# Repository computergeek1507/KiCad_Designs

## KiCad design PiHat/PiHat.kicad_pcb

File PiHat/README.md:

# Copyright and Disclaimer
Copyright: Scott Hanson

This documentation describes Open Hardware and is licensed under the CERN OHL v. 1.2.

You may redistribute and modify this documentation under the terms of the CERN OHL v.1.2. (http://ohwr.org/cernohl). This documentation is distributed WITHOUT ANY EXPRESS OR IMPLIED WARRANTY, INCLUDING OF MERCHANTABILITY, SATISFACTORY QUALITY AND FITNESS FOR A PARTICULAR PURPOSE. Please see the CERN OHL v.1.2 for applicable conditions

# Open Source PiHat

Open Source Pixel PiHat. A Raspberry Pi running FPP can drives 2 pixel ports and 1 serial port. The design was made with all through hole components for easy assembly by most users. Open source applications were used to create this controller. [KiCad](http://kicad-pcb.org/) was used for the PCB design, and [LibreOffice](https://www.libreoffice.org/) for the documentation.

To order your own PCB upload the gerber.zip file to your favorite PCB manufacture of choice, I personally use [jlcpcb.com](https://jlcpcb.com/).

Assembly Instructions are included in the manual below.

### Features
* Powered by FPP Falcon Player
* Standalone/Master/Remote/Bridge Support
* 2 3-Wire Pixel Ports
* 700 pixel per output at 40 FPS or 1300 at 20 FPS
* 1 DMX Serial Outputs
* Fused Powered DMX Output
* OLED Display header
* Adafruit Real Time Clock Header Connector
* 2 pin GPIO Header for Push Button or Relay Support
* 5v - 24v Vin Support

## [Part BOM](https://github.com/computergeek1507/KiCad_Designs/raw/master/PiHat/PiHat_BOM.ods)

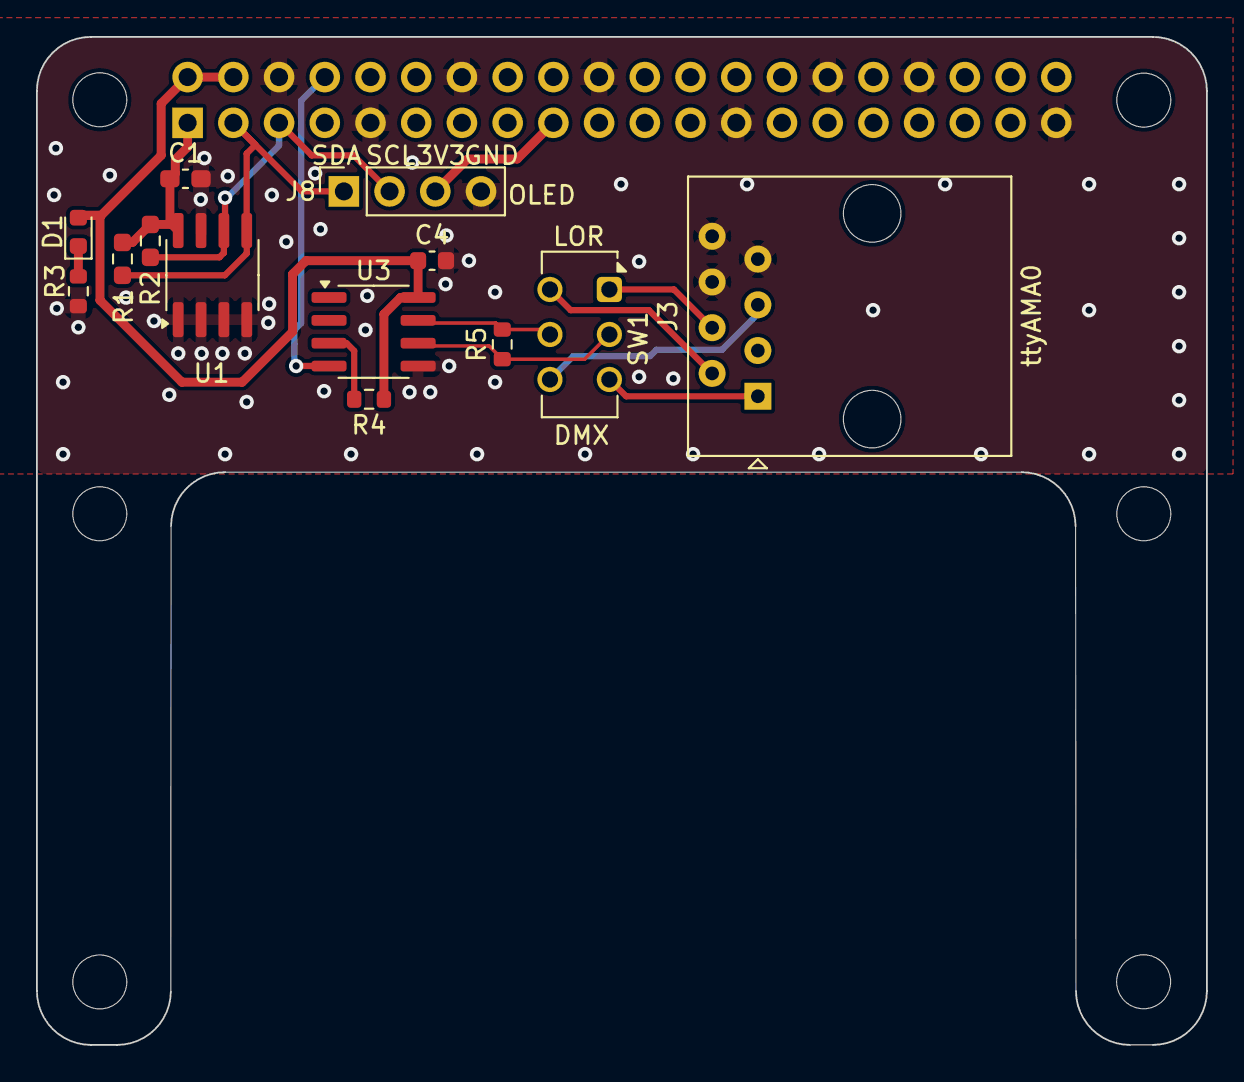
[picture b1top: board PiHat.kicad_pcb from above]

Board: 2 copper layers, 65.0 x 56.0 mm, 20 parts (1 on the bottom side), 14 nets.

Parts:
C1: 0.1uF; C_0603_1608Metric_Pad1.08x0.95mm_HandSolder
C4: 0.1uF; C_0603_1608Metric
D1: LED; LED_0603_1608Metric
H1, H2, H3, H4, H5, H6: 3mm_Mounting_Hole; MountingHole_3mm
J1: Raspberry_Pi_2_3; PinSocket_2x20_P2.54mm_Vertical
J3: DMX1 RJ45; RJ45_Amphenol_54602-x08_Horizontal
J8: OLED; PinSocket_1x04_P2.54mm_Vertical
R1, R2: 4.7K; R_0603_1608Metric_Pad0.98x0.95mm_HandSolder
R3, R5: 120; R_0603_1608Metric
R4: 10K; R_0603_1608Metric
SW1: DMX_LOR_Select; SW_CK_JS202011CQN_DPDT_Straight
U1: 24LC256; SOIC-8_3.9x4.9mm_P1.27mm
U3: SP3485CP; SOIC-8_3.9x4.9mm_P1.27mm

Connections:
+3.3V: C1.1, J1.1 (3V3), J1.17 (3V3), J8.3, R1.2, R2.2, U1.8 (VCC)
+5V: C4.1, D1.2 (A), J1.2 (5V), J1.4 (5V), R4.1, U3.8 (VCC)
/DMX+: R5.1, SW1.2 (B), U3.6 (A)
/DMX-: R5.2, SW1.5 (B), U3.7 (B)
GND: C1.2, C4.2, J1.6 (GND), J1.9 (GND), J1.14 (GND), J1.20 (GND), J1.25 (GND), J1.30 (GND), J1.34 (GND), J1.39 (GND), J3.6, J3.7, J3.8, J8.4, R3.2, U1.1 (A0), U1.2 (A1), U1.3 (A2), U1.4 (GND), U1.7 (WP), U3.5 (GND)
I2C_SCL: J1.5 (SCL/GPIO3), J8.2, R2.1, U1.6 (SCL)
I2C_SDA: J1.3 (SDA/GPIO2), J8.1, R1.1, U1.5 (SDA)
unnamed: D1.1 (K), R3.1
unnamed: J3.4, SW1.1 (A)
unnamed: J3.1, SW1.3 (C)
unnamed: J3.5, SW1.4 (A)
unnamed: J3.2, SW1.6 (C)
unnamed: R4.2, U3.3 (DE)
TXD: J1.8 (GPIO14/TXD), U3.4 (DI)

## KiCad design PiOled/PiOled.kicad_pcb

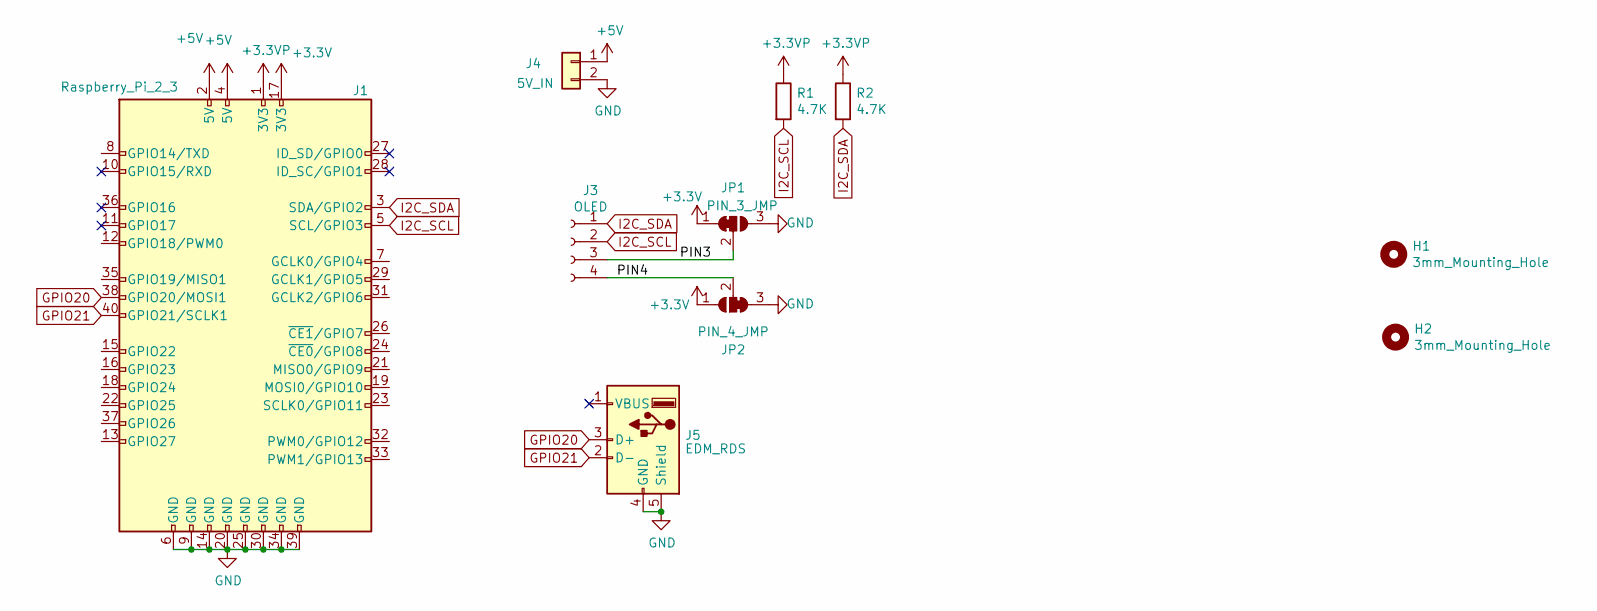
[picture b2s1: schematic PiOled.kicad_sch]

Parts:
H1, H2: 3mm_Mounting_Hole; MountingHole_3mm
J1: Raspberry_Pi_2_3; PinSocket_2x20_P2.54mm_Vertical; MPN PPPC202LFBN-RC; Digi-Key_PN S7123-ND
J3: OLED; PinSocket_1x04_P2.54mm_Vertical; MPN PPTC041LFBN-RC; Digi-Key_PN S7002-ND
J4: 5V_IN; TerminalBlock_Phoenix_MKDS-1,5-2_1x02_P5.00mm_Horizontal; MPN ED2675-ND; Digi-Key_PN OSTT7020150
J5: EDM_RDS; USB_A_Molex_67643_Horizontal
JP1: PIN_3_JMP; SolderJumper-3_P1mm_Bridged12
JP2: PIN_4_JMP; SolderJumper-3_P1mm_Bridged23
R1, R2: 4.7K; R_0805_2012Metric_Pad1.20x1.40mm_HandSolder

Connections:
+3.3VP: J1.1 (3V3), R1.1, R2.1
+3V3: J1.17 (3V3), JP1.1 (A), JP2.1 (A)
+5V: J1.2 (5V), J1.4 (5V), J4.1
/PIN3: J3.3, JP1.2 (C)
/PIN4: J3.4, JP2.2 (C)
GND: J1.6 (GND), J1.9 (GND), J1.14 (GND), J1.20 (GND), J1.25 (GND), J1.30 (GND), J1.34 (GND), J1.39 (GND), J4.2, J5.4 (GND), J5.5 (Shield), JP1.3 (B), JP2.3 (B)
GPIO20: J1.38 (GPIO20/MOSI1), J5.3 (D+)
GPIO21: J1.40 (GPIO21/SCLK1), J5.2 (D-)
I2C_SCL: J1.5 (SCL/GPIO3), J3.2, R1.2
I2C_SDA: J1.3 (SDA/GPIO2), J3.1, R2.2

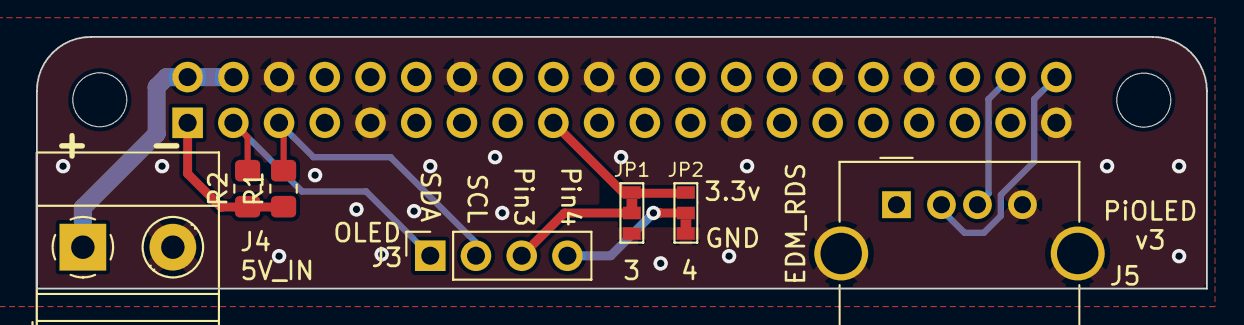
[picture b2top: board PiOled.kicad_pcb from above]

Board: 2 copper layers, 65.0 x 14.0 mm, 10 parts (1 on the bottom side), 10 nets.

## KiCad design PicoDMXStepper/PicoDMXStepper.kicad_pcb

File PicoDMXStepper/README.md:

# Copyright and Disclaimer
Copyright: Scott Hanson

This documentation describes Open Hardware and is licensed under the CERN OHL v. 1.2.

You may redistribute and modify this documentation under the terms of the CERN OHL v.1.2. (http://ohwr.org/cernohl). This documentation is distributed WITHOUT ANY EXPRESS OR IMPLIED WARRANTY, INCLUDING OF MERCHANTABILITY, SATISFACTORY QUALITY AND FITNESS FOR A PARTICULAR PURPOSE. Please see the CERN OHL v.1.2 for applicable conditions

# Pico DMX to Stepper

Drive Stepper Moter With DMX. SW2 configures steps per DMX Value. Open source applications were used to create this controller. [KiCad](http://kicad-pcb.org/) was used for the PCB design, and [LibreOffice](https://www.libreoffice.org/) for the documentation.

To order your own PCB upload the gerber.zip file to your favorite PCB manufacture of choice, I personally use [jlcpcb.com](https://jlcpcb.com/).

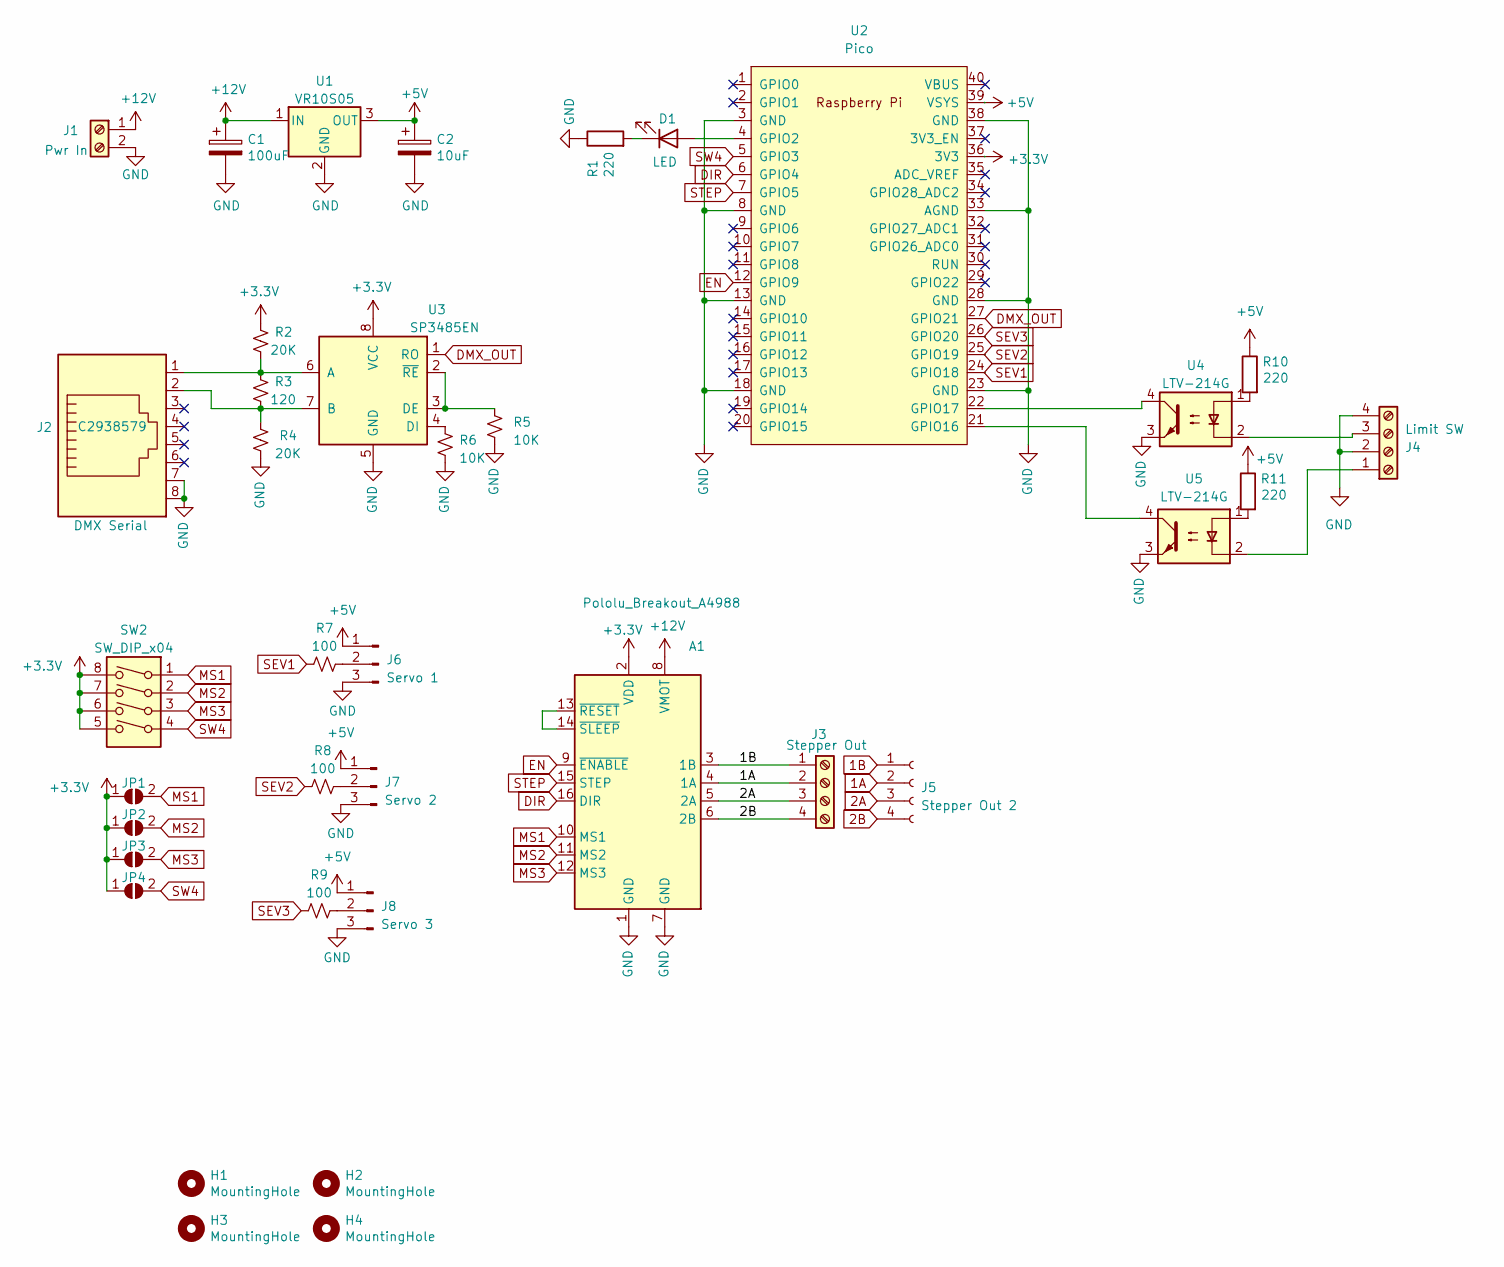
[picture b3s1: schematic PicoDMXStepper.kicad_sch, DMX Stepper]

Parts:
A1: Pololu_Breakout_A4988; Pololu_Breakout-16_15.2x20.3mm
C1: 100uF; C_Elec_8x10.2; LCSC C445063
C2: 10uF; C_0603_1608Metric_Pad1.08x0.95mm_HandSolder; LCSC C19702
D1: LED; LED_0603_1608Metric_Pad1.05x0.95mm_HandSolder; LCSC C72043
H1, H2, H3, H4: MountingHole; MountingHole_3.7mm
J1: Pwr In; BARRIER_BLOCK_1ROW_2POS_P8.26MM; LCSC C306200
J2: DMX Serial; RJ45_Amphenol_54602-x08_Horizontal; LCSC C2938579
J3: Stepper Out; TerminalBlock_Phoenix_MKDS-1,5-4_1x04_P5.00mm_Horizontal; LCSC C192779
J4: Limit SW; PhoenixContact_MCV_1,5_4-G-3.81_1x04_P3.81mm_Vertical; LCSC_PN C430599
J5: Stepper Out 2; JST_XH_B4B-XH-A_1x04_P2.50mm_Vertical
J6: Servo 1; PinHeader_1x03_P2.54mm_Vertical
J7: Servo 2; PinHeader_1x03_P2.54mm_Vertical
J8: Servo 3; PinHeader_1x03_P2.54mm_Vertical
JP1: MS1; SolderJumper-2_P1.3mm_Open_Pad1.0x1.5mm
JP2: MS2; SolderJumper-2_P1.3mm_Open_Pad1.0x1.5mm
JP3: MS3; SolderJumper-2_P1.3mm_Open_Pad1.0x1.5mm
JP4: SW4; SolderJumper-2_P1.3mm_Open_Pad1.0x1.5mm
R1, R10, R11: 220; R_0603_1608Metric_Pad0.98x0.95mm_HandSolder; LCSC C23345
R2, R4: 20K; R_0603_1608Metric_Pad0.98x0.95mm_HandSolder; LCSC_PN C4184
R3: 120; R_0603_1608Metric_Pad0.98x0.95mm_HandSolder; LCSC C72043
R5, R6: 10K; R_0603_1608Metric_Pad0.98x0.95mm_HandSolder; LCSC C25804
R7, R8, R9: 100; R_0603_1608Metric_Pad0.98x0.95mm_HandSolder
SW2: SW_DIP_x04; SW_DIP_SPSTx04_Slide_6.7x11.72mm_W7.62mm_P2.54mm_LowProfile; LCSC C509571
U1: VR10S05; MPN VR10S05; Digi-Key_PN 1470-VR10S05-ND
U2: Pico; RPi_Pico_SMD_TH
U3: SP3485EN; SOIC-8_3.9x4.9mm_P1.27mm; LCSC_PN C8963
U4, U5: LTV-214G; LTV214; LCSC C133122

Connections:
1A: A1.4 (1A), J3.2, J5.2
1B: A1.3 (1B), J3.1, J5.1
2A: A1.5 (2A), J3.3, J5.3
2B: A1.6 (2B), J3.4, J5.4
+3V3: A1.2 (VDD), JP1.1 (A), JP2.1 (A), JP3.1 (A), JP4.1 (A), R2.1, SW2.5, SW2.6, SW2.7, SW2.8, U2.36 (3V3), U3.8 (VCC)
+5V: C2.1, J6.1, J7.1, J8.1, R10.1, R11.1, U1.3 (OUT), U2.39 (VSYS)
+12V: A1.8 (VMOT), C1.1, J1.1, U1.1 (IN)
DIR: A1.16 (DIR), U2.6 (GPIO4)
DMX_OUT: U2.27 (GPIO21), U3.1 (RO)
EN: A1.9 (~ENABLE), U2.12 (GPIO9)
GND: A1.1 (GND), A1.7 (GND), C1.2, C2.2, J1.2, J2.7, J2.8, J4.2, J4.4, J6.3, J7.3, J8.3, R1.1, R4.2, R5.2, R6.2, U1.2 (GND), U2.3 (GND), U2.8 (GND), U2.13 (GND), U2.18 (GND), U2.23 (GND), U2.28 (GND), U2.33 (AGND), U2.38 (GND), U3.5 (GND), U4.3, U5.3
MS1: A1.10 (MS1), JP1.2 (B), SW2.1
MS2: A1.11 (MS2), JP2.2 (B), SW2.2
MS3: A1.12 (MS3), JP3.2 (B), SW2.3
unnamed: A1.13 (~RESET), A1.14 (~SLEEP)
unnamed: D1.2 (A), U2.4 (GPIO2)
unnamed: D1.1 (K), R1.2
unnamed: J4.1, U5.2
unnamed: J4.3, U4.2
unnamed: J6.2, R7.2
unnamed: J7.2, R8.2
unnamed: J8.2, R9.2
unnamed: R10.2, U4.1
unnamed: R11.2, U5.1
unnamed: U2.21 (GPIO16), U5.4
unnamed: U2.22 (GPIO17), U4.4
unnamed: J2.1, R2.2, R3.1, U3.6 (A)
unnamed: J2.2, R3.2, R4.1, U3.7 (B)
unnamed: R5.1, U3.2 (~RE), U3.3 (DE)
unnamed: R6.1, U3.4 (DI)
SEV1: R7.1, U2.24 (GPIO18)
SEV2: R8.1, U2.25 (GPIO19)
SEV3: R9.1, U2.26 (GPIO20)
STEP: A1.15 (STEP), U2.7 (GPIO5)
SW4: JP4.2 (B), SW2.4, U2.5 (GPIO3)

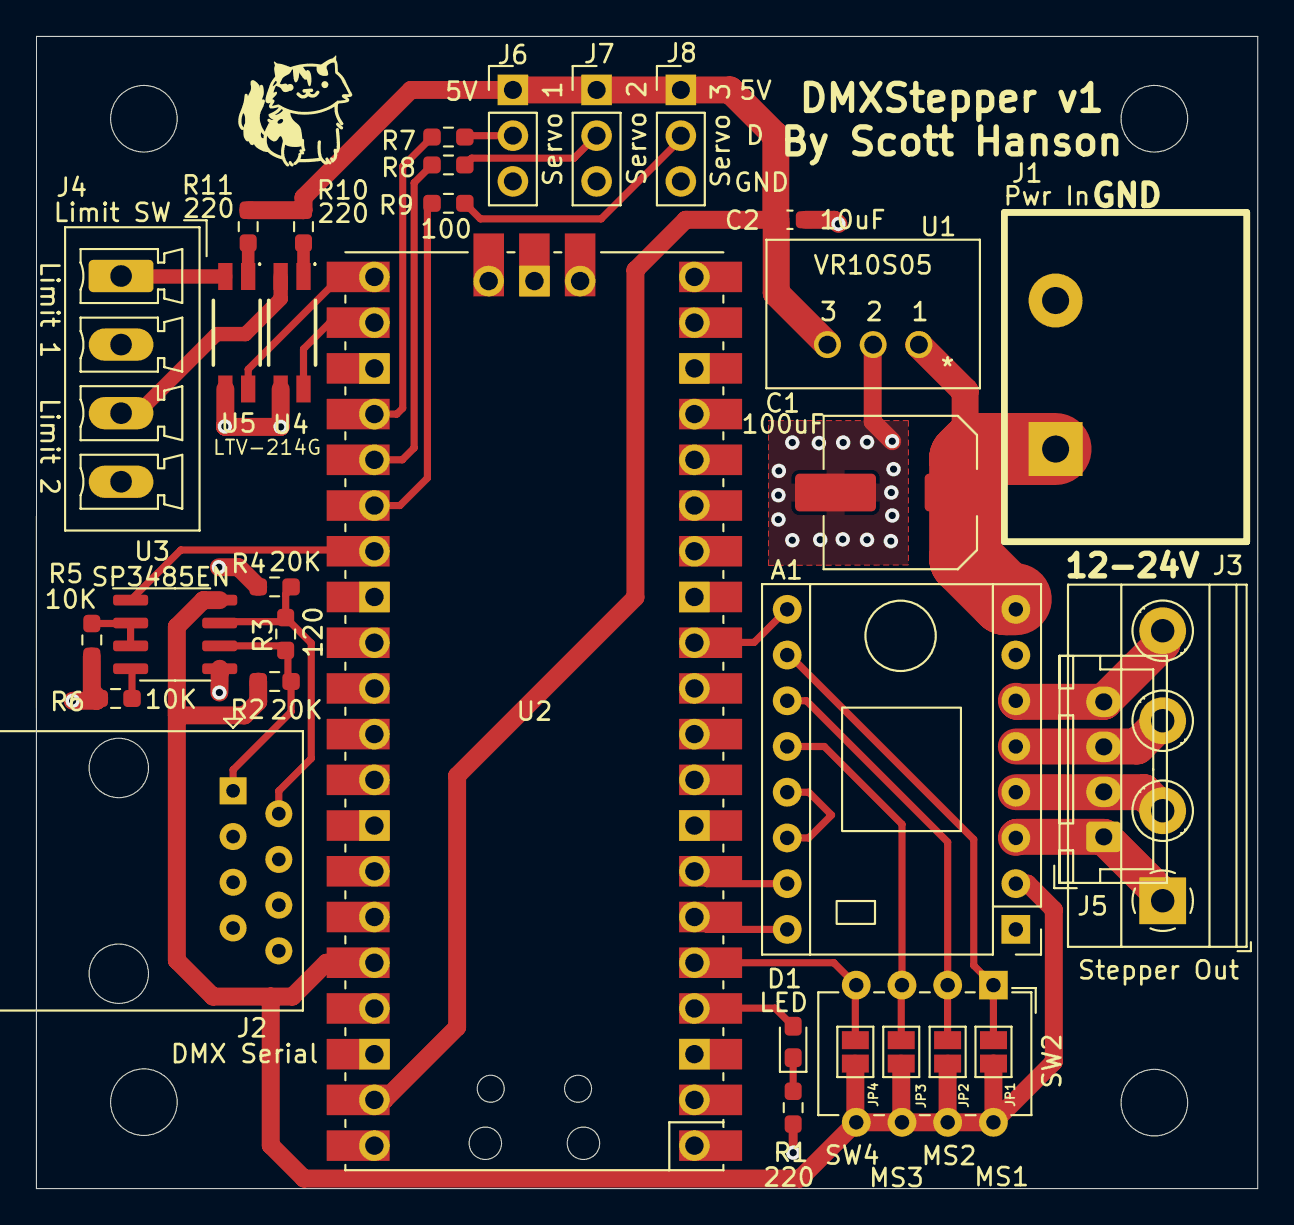
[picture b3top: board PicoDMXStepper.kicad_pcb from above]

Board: 2 copper layers, 67.8 x 64.0 mm, 37 parts (0 on the bottom side), 35 nets.

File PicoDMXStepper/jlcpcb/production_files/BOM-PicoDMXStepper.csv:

Comment,Designator,Footprint,LCSC
Servo 1,"J6,J7,J8",PinHeader_1x03_P2.54mm_Vertical,C124376
LTV-214G,"U4,U5",LTV214,C133122
Stepper Out 2,J5,JST_XH_B4B-XH-A_1x04_P2.50mm_Vertical,C144395
Stepper Out,J3,"TerminalBlock_Phoenix_MKDS-1,5-4_1x04_P5.00mm_Horizontal",C192779
10uF,C2,C_0603_1608Metric_Pad1.08x0.95mm_HandSolder,C19702
100,"R7,R8,R9",R_0603_1608Metric_Pad0.98x0.95mm_HandSolder,C22775
120,R3,R_0603_1608Metric_Pad0.98x0.95mm_HandSolder,C22787
220,"R1,R10,R11",R_0603_1608Metric_Pad0.98x0.95mm_HandSolder,C23345
10K,"R5,R6",R_0603_1608Metric_Pad0.98x0.95mm_HandSolder,C25804
DMX Serial,J2,RJ45_Amphenol_54602-x08_Horizontal,C2938579
Pwr In,J1,BARRIER_BLOCK_1ROW_2POS_P8.26MM,C306200
20K,"R2,R4",R_0603_1608Metric_Pad0.98x0.95mm_HandSolder,C4184
100uF,C1,C_Elec_8x10.2,C445063
SW_DIP_x04,SW2,SW_DIP_SPSTx04_Slide_6.7x11.72mm_W7.62mm_P2.54mm_LowProfile,C509571
Limit SW,J4,"PhoenixContact_MCV_1,5_4-G-3.81_1x04_P3.81mm_Vertical",C69809
LED,D1,LED_0603_1608Metric_Pad1.05x0.95mm_HandSolder,C72043
SP3485EN,U3,SOIC-8_3.9x4.9mm_P1.27mm,C8963
Pololu_Breakout_A4988,A1,Pololu_Breakout-16_15.2x20.3mm,
Pico,U2,RPi_Pico_SMD_TH,
VR10S05,U1,VR10S05,

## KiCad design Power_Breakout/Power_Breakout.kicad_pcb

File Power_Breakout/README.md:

# Copyright and Disclaimer
Copyright: Scott Hanson

This documentation describes Open Hardware and is licensed under the CERN OHL v. 1.2.

You may redistribute and modify this documentation under the terms of the CERN OHL v.1.2. (http://ohwr.org/cernohl). This documentation is distributed WITHOUT ANY EXPRESS OR IMPLIED WARRANTY, INCLUDING OF MERCHANTABILITY, SATISFACTORY QUALITY AND FITNESS FOR A PARTICULAR PURPOSE. Please see the CERN OHL v.1.2 for applicable conditions

# Power Breakout

Power Breakout Board for HP Power Supply

# BOM
| Component | Qty | Description              | Digi-Key PN     | Manufacturer          | Manufacturer PN |
|-----------|-----|--------------------------|-----------------|-----------------------|-----------------|
| J1,J2     |  2  | CONN 4 POS STRIP 0.374"  | ED2955-ND       | On Shore Technology   | OSTYK51104030   |
| J3        |  1  | CONN EDGE DUAL 64POS 0.1 | 1761469-1-ND    | TE Connectivity       | 1761469-1       |
| R1        |  1  | RES 120 OHM 1/4W 5%      | CF14JT120RCT-ND | Stackpole Electronics | CF14JT120R      |
| SW1       |  1  | SWITCH SLIDE SPDT        | 679-1849-ND     | APEM                  | MHSS1105        |

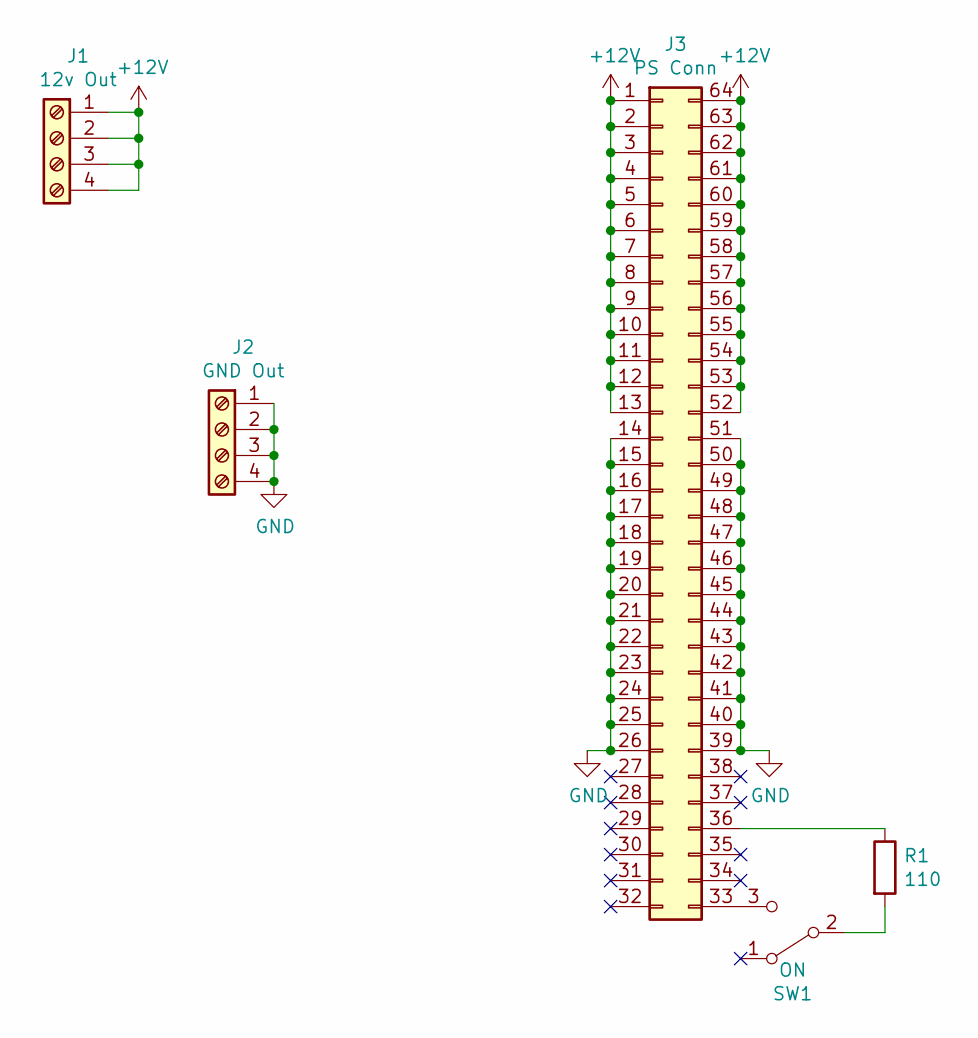
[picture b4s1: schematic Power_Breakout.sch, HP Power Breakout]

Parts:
J1: 12v Out; BARRIER_BLOCK_1ROW_4POS_P9.5MM
J2: GND Out; BARRIER_BLOCK_1ROW_4POS_P9.5MM
J3: PS Conn; TE_1761469-1
R1: 110; R_Axial_DIN0207_L6.3mm_D2.5mm_P7.62mm_Horizontal
SW1: ON; switch_mmp122-r

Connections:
+12V: J1.1, J1.2, J1.3, J1.4, J3.1, J3.2, J3.3, J3.4, J3.5, J3.6, J3.7, J3.8, J3.9, J3.10, J3.11, J3.12, J3.13, J3.52, J3.53, J3.54, J3.55, J3.56, J3.57, J3.58, J3.59, J3.60, J3.61, J3.62, J3.63, J3.64
GND: J2.1, J2.2, J2.3, J2.4, J3.14, J3.15, J3.16, J3.17, J3.18, J3.19, J3.20, J3.21, J3.22, J3.23, J3.24, J3.25, J3.26, J3.39, J3.40, J3.41, J3.42, J3.43, J3.44, J3.45, J3.46, J3.47, J3.48, J3.49, J3.50, J3.51
unnamed: J3.33, SW1.3 (C)
unnamed: J3.36, R1.1
unnamed: R1.2, SW1.2 (B)

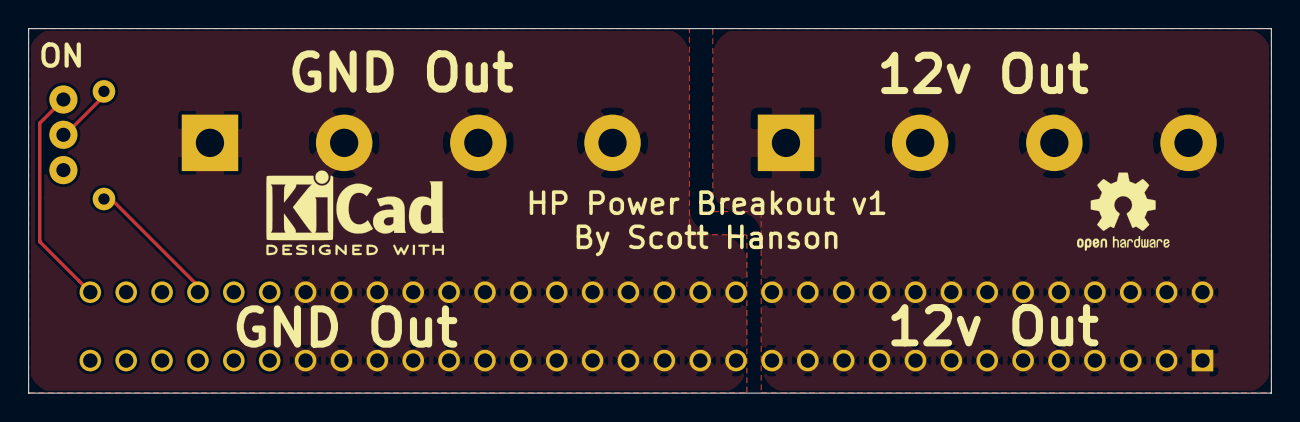
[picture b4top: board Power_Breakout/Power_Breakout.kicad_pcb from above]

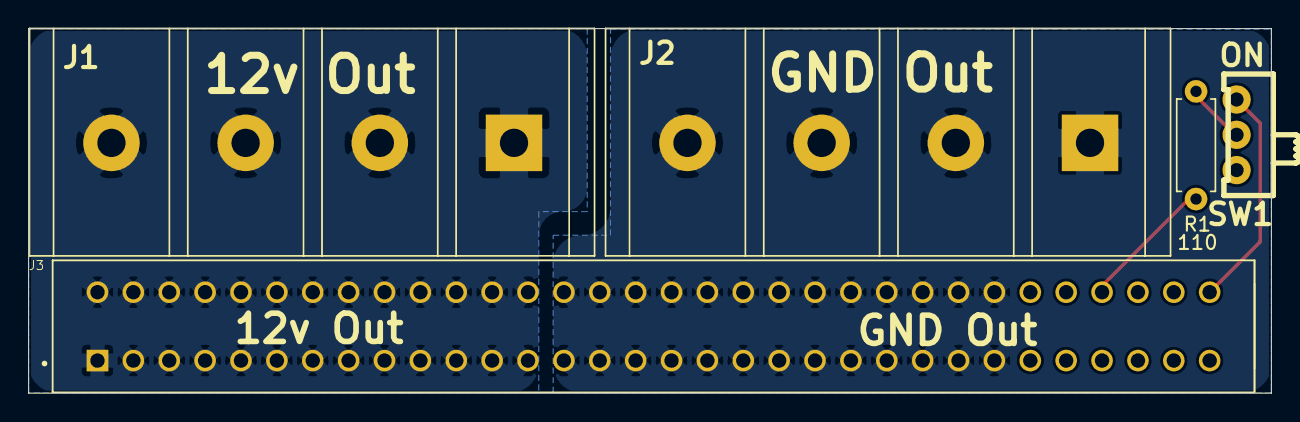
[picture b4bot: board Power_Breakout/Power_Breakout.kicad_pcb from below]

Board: 2 copper layers, 88.0 x 25.8 mm, 5 parts (5 on the bottom side), 5 nets.

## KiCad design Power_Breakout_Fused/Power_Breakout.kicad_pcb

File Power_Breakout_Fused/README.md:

# Copyright and Disclaimer
Copyright: Scott Hanson

This documentation describes Open Hardware and is licensed under the CERN OHL v. 1.2.

You may redistribute and modify this documentation under the terms of the CERN OHL v.1.2. (http://ohwr.org/cernohl). This documentation is distributed WITHOUT ANY EXPRESS OR IMPLIED WARRANTY, INCLUDING OF MERCHANTABILITY, SATISFACTORY QUALITY AND FITNESS FOR A PARTICULAR PURPOSE. Please see the CERN OHL v.1.2 for applicable conditions

# Power Breakout

Power Fused Breakout Board for HP Power Supply

# BOM
| Component   | Qty | Description              | Digi-Key PN     | Manufacturer          | Manufacturer PN |
|-------------|-----|--------------------------|-----------------|-----------------------|-----------------|
| D1          |  1  | LED GREEN 3MM            | 732-5008-ND     | Würth Elektronik      | 151031VS06000   |
| J1,J2       |  2  | CONN 4 POS STRIP 0.374"  | ED2955-ND       | On Shore Technology   | OSTYK51104030   |
| F1,F2,F3,F4 |  4  | FUSE HOLDER BLADE 30A    | 36-3568-ND      | Keystone Electronics  | 3568            |
| F1,F2,F3,F4 |  4  | FUSE AUTO 15A BLADE MINI | F992-ND         | Littelfuse            | 0297015.WXNV    |
| J3          |  1  | CONN EDGE DUAL 64POS 0.1 | 1761469-1-ND    | TE Connectivity       | 1761469-1       |
| R1          |  1  | RES 120 OHM 1/4W 5%      | CF14JT120RCT-ND | Stackpole Electronics | CF14JT120R      |
| R2          |  1  | RES 1K OHM 1/4W 5%       | CF14JT1K00CT-ND | Stackpole Electronics | CF14JT1K00      |
| SW1         |  1  | SWITCH SLIDE SPDT        | 679-1849-ND     | APEM                  | MHSS1105        |

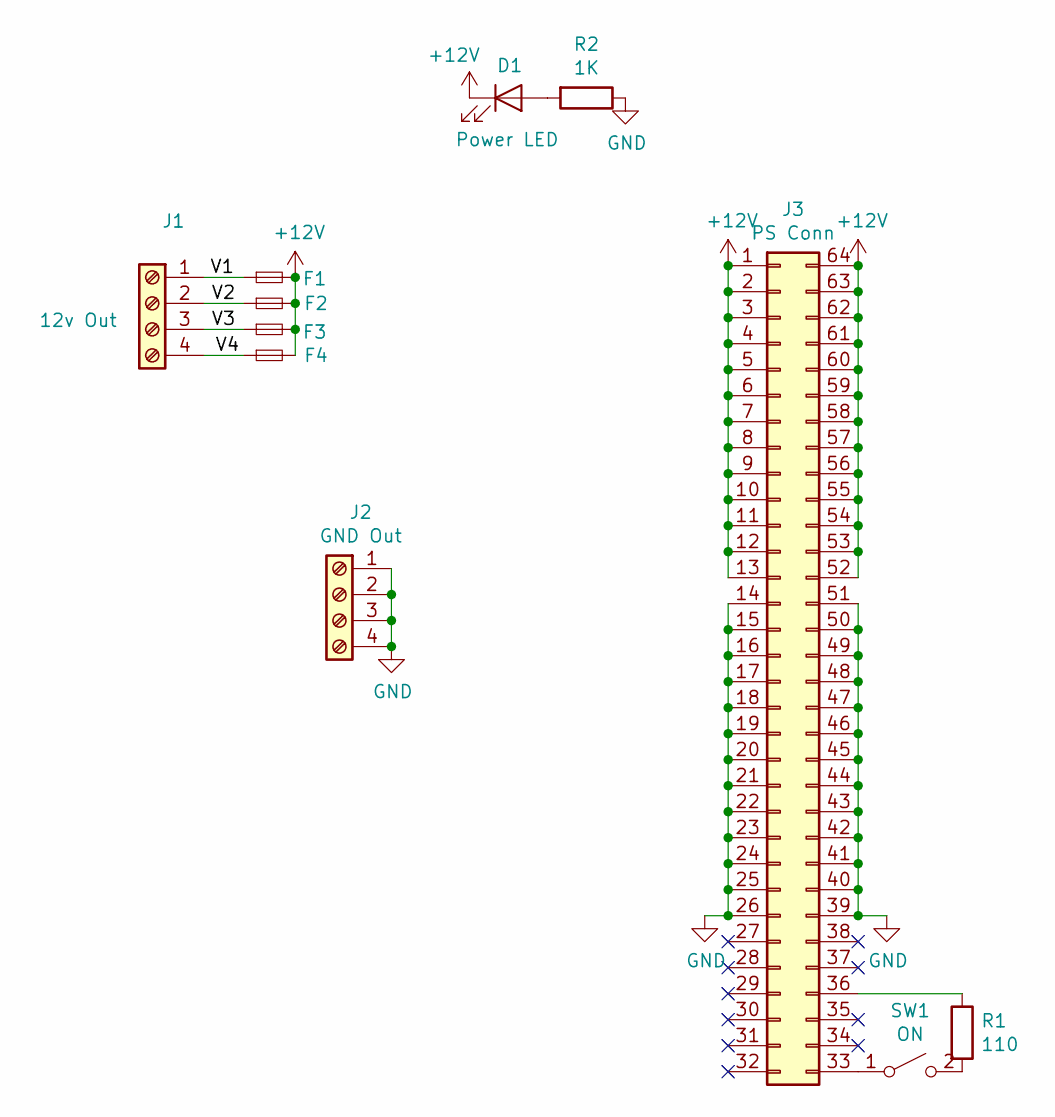
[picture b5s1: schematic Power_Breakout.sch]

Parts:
D1: Power LED; LED_D3.0mm_Clear
F1, F2, F3, F4: Fuse_Small; Fuseholder_Blade_Mini_Keystone_3568
J1: 12v Out; BARRIER_BLOCK_1ROW_4POS_P9.5MM
J2: GND Out; BARRIER_BLOCK_1ROW_4POS_P9.5MM
J3: PS Conn; TE_1761469-1
R1: 110; R_Axial_DIN0207_L6.3mm_D2.5mm_P7.62mm_Horizontal
R2: 1K; R_Axial_DIN0207_L6.3mm_D2.5mm_P7.62mm_Horizontal
SW1: ON; switch_mmp122-r

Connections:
+12V: D1.1 (K), F1.2, F2.2, F3.2, F4.2, J3.1, J3.2, J3.3, J3.4, J3.5, J3.6, J3.7, J3.8, J3.9, J3.10, J3.11, J3.12, J3.13, J3.52, J3.53, J3.54, J3.55, J3.56, J3.57, J3.58, J3.59, J3.60, J3.61, J3.62, J3.63, J3.64
/V1: F1.1, J1.1
/V2: F2.1, J1.2
/V3: F3.1, J1.3
/V4: F4.1, J1.4
GND: J2.1, J2.2, J2.3, J2.4, J3.14, J3.15, J3.16, J3.17, J3.18, J3.19, J3.20, J3.21, J3.22, J3.23, J3.24, J3.25, J3.26, J3.39, J3.40, J3.41, J3.42, J3.43, J3.44, J3.45, J3.46, J3.47, J3.48, J3.49, J3.50, J3.51, R2.1
unnamed: D1.2 (A), R2.2
unnamed: J3.33, SW1.1 (A)
unnamed: J3.36, R1.1
unnamed: R1.2, SW1.2 (B)

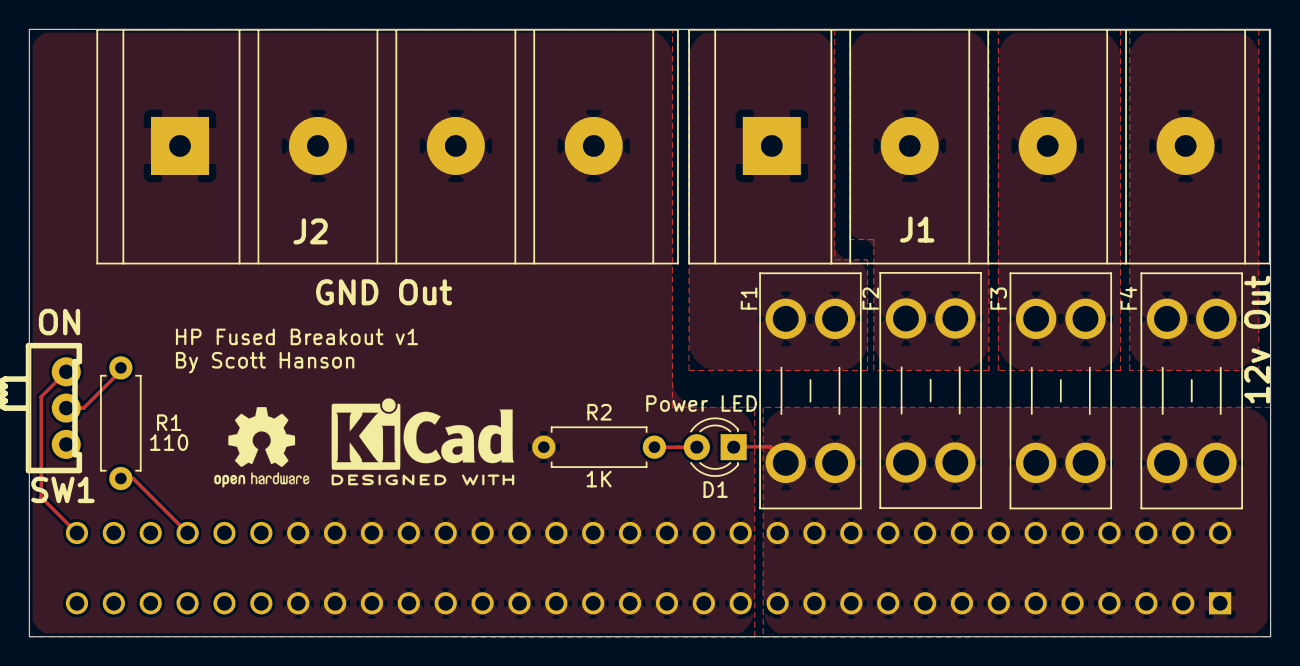
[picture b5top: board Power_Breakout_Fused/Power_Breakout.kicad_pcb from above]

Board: 2 copper layers, 85.5 x 41.8 mm, 11 parts (1 on the bottom side), 10 nets.

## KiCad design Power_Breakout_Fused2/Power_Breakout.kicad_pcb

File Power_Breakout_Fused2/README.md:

# Copyright and Disclaimer
Copyright: Scott Hanson

This documentation describes Open Hardware and is licensed under the CERN OHL v. 1.2.

You may redistribute and modify this documentation under the terms of the CERN OHL v.1.2. (http://ohwr.org/cernohl). This documentation is distributed WITHOUT ANY EXPRESS OR IMPLIED WARRANTY, INCLUDING OF MERCHANTABILITY, SATISFACTORY QUALITY AND FITNESS FOR A PARTICULAR PURPOSE. Please see the CERN OHL v.1.2 for applicable conditions

# Fused Power Breakout

Power Fused Breakout Board for HP Power Supply
<!--
# BOM
| Component   | Qty | Description              | Digi-Key PN     | Manufacturer          | Manufacturer PN |
|-------------|-----|--------------------------|-----------------|-----------------------|-----------------|
| D1          |  1  | LED GREEN 3MM            | 732-5008-ND     | Würth Elektronik      | 151031VS06000   |
| J1,J2       |  2  | CONN 4 POS STRIP 0.374"  | ED2955-ND       | On Shore Technology   | OSTYK51104030   |
| F1,F2,F3,F4 |  4  | FUSE HOLDER BLADE 30A    | 36-3568-ND      | Keystone Electronics  | 3568            |
| F1,F2,F3,F4 |  4  | FUSE AUTO 15A BLADE MINI | F992-ND         | Littelfuse            | 0297015.WXNV    |
| J3          |  1  | CONN EDGE DUAL 64POS 0.1 | 1761469-1-ND    | TE Connectivity       | 1761469-1       |
| R1          |  1  | RES 120 OHM 1/4W 5%      | CF14JT120RCT-ND | Stackpole Electronics | CF14JT120R      |
| R2          |  1  | RES 1K OHM 1/4W 5%       | CF14JT1K00CT-ND | Stackpole Electronics | CF14JT1K00      |
-->

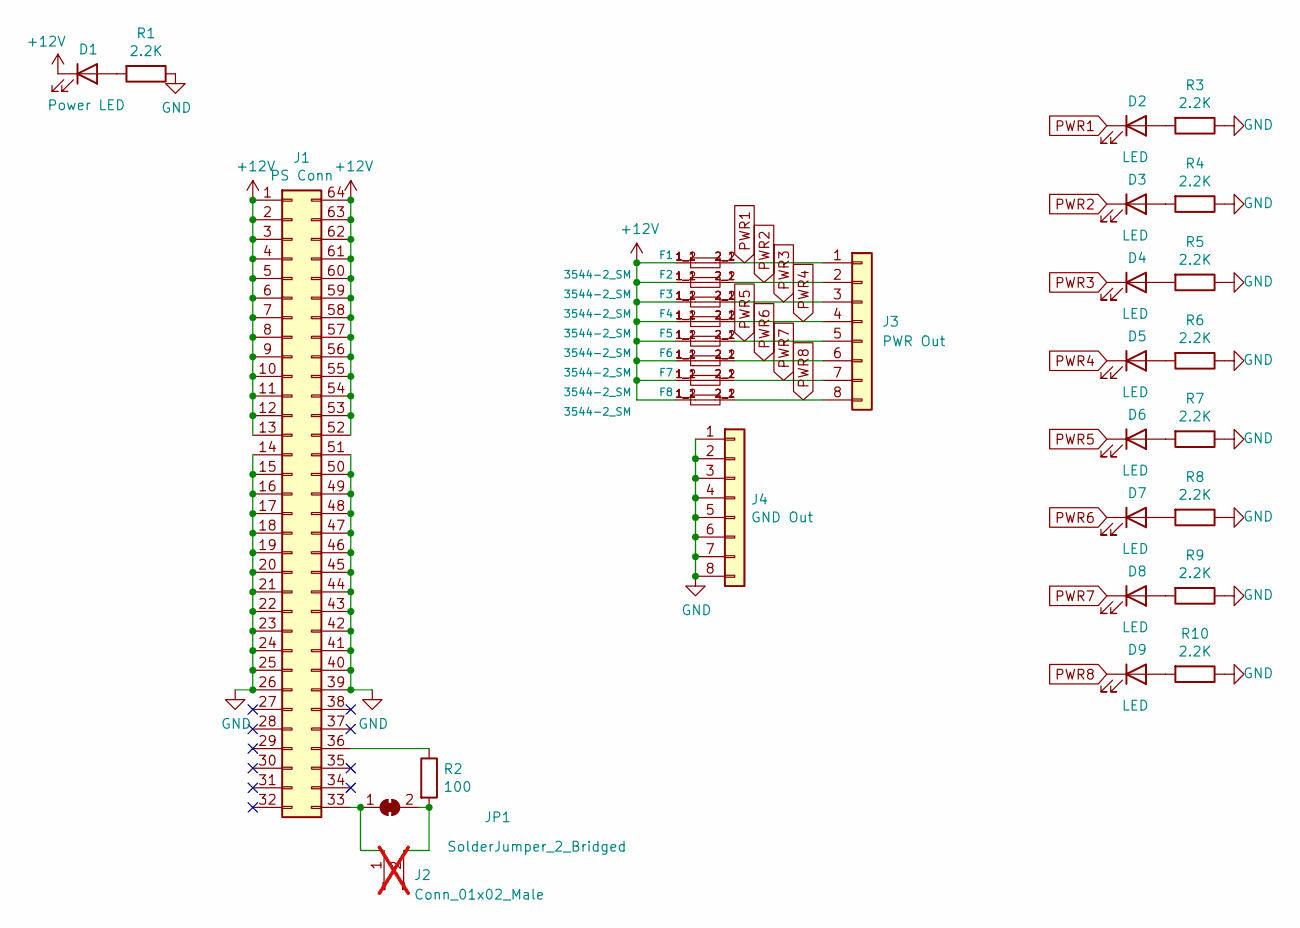
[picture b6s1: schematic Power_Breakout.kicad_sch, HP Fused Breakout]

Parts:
D1: Power LED; LED_0603_1608Metric; MPN LTST-C190KRKT; Digi-Key PN 160-1436-1-ND
D2, D3, D4, D5, D6, D7, D8, D9: LED; LED_0402_1005Metric; MPN QBLP595-IG; Digi-Key PN 1516-1216-1-ND
F1, F2, F3, F4, F5, F6, F7, F8: 3544-2_SM; FUSE_3544-2; MPN 3544-2; Digi-Key PN 36-3544-2-ND
J1: PS Conn; TE_1761469-1; MPN 1761468-1; Digi-Key PN A102052-ND
J2: Conn_01x02_Male; PinHeader_1x02_P2.54mm_Vertical; not fitted
J3: PWR Out; PhoenixContact_MCV_1,5_8-G-5.08_1x08_P5.08mm_Vertical; MPN VI0821550000G; Digi-Key PN 609-3942-ND
J4: GND Out; PhoenixContact_MCV_1,5_8-G-5.08_1x08_P5.08mm_Vertical; MPN VI0821550000G; Digi-Key PN 609-3942-ND
JP1: SolderJumper_2_Bridged; SolderJumper-2_P1.3mm_Bridged_Pad1.0x1.5mm
R1: 2.2K; R_0603_1608Metric; MPN RC0603FR-072K2L; Digi-Key PN 311-2.20KHRCT-ND
R2: 100; R_0603_1608Metric; MPN RC0603FR-07100RL; Digi-Key PN 311-100HRCT-ND
R3, R4, R5, R6, R7, R8, R9, R10: 2.2K; R_0402_1005Metric; MPN RC0402FR-072K2L; Digi-Key PN 311-2.20KLRCT-ND

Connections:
+12V: D1.1 (K), F1.1_1 (1), F1.1_2 (1), F2.1_1 (1), F2.1_2 (1), F3.1_1 (1), F3.1_2 (1), F4.1_1 (1), F4.1_2 (1), F5.1_1 (1), F5.1_2 (1), F6.1_1 (1), F6.1_2 (1), F7.1_1 (1), F7.1_2 (1), F8.1_1 (1), F8.1_2 (1), J1.1, J1.2, J1.3, J1.4, J1.5, J1.6, J1.7, J1.8, J1.9, J1.10, J1.11, J1.12, J1.13, J1.52, J1.53, J1.54, J1.55, J1.56, J1.57, J1.58, J1.59, J1.60, J1.61, J1.62, J1.63, J1.64
GND: J1.14, J1.15, J1.16, J1.17, J1.18, J1.19, J1.20, J1.21, J1.22, J1.23, J1.24, J1.25, J1.26, J1.39, J1.40, J1.41, J1.42, J1.43, J1.44, J1.45, J1.46, J1.47, J1.48, J1.49, J1.50, J1.51, J4.1, J4.2, J4.3, J4.4, J4.5, J4.6, J4.7, J4.8, R1.1, R3.1, R4.1, R5.1, R6.1, R7.1, R8.1, R9.1, R10.1
unnamed: D1.2 (A), R1.2
unnamed: D2.2 (A), R3.2
unnamed: D3.2 (A), R4.2
unnamed: D4.2 (A), R5.2
unnamed: D5.2 (A), R6.2
unnamed: D6.2 (A), R7.2
unnamed: D7.2 (A), R8.2
unnamed: D8.2 (A), R9.2
unnamed: D9.2 (A), R10.2
unnamed: J1.33, J2.1, JP1.1 (A)
unnamed: J1.36, R2.1
unnamed: J2.2, JP1.2 (B), R2.2
PWR1: D2.1 (K), F1.2_1 (2), F1.2_2 (2), J3.1
PWR2: D3.1 (K), F2.2_1 (2), F2.2_2 (2), J3.2
PWR3: D4.1 (K), F3.2_1 (2), F3.2_2 (2), J3.3
PWR4: D5.1 (K), F4.2_1 (2), F4.2_2 (2), J3.4
PWR5: D6.1 (K), F5.2_1 (2), F5.2_2 (2), J3.5
PWR6: D7.1 (K), F6.2_1 (2), F6.2_2 (2), J3.6
PWR7: D8.1 (K), F7.2_1 (2), F7.2_2 (2), J3.7
PWR8: D9.1 (K), F8.2_1 (2), F8.2_2 (2), J3.8

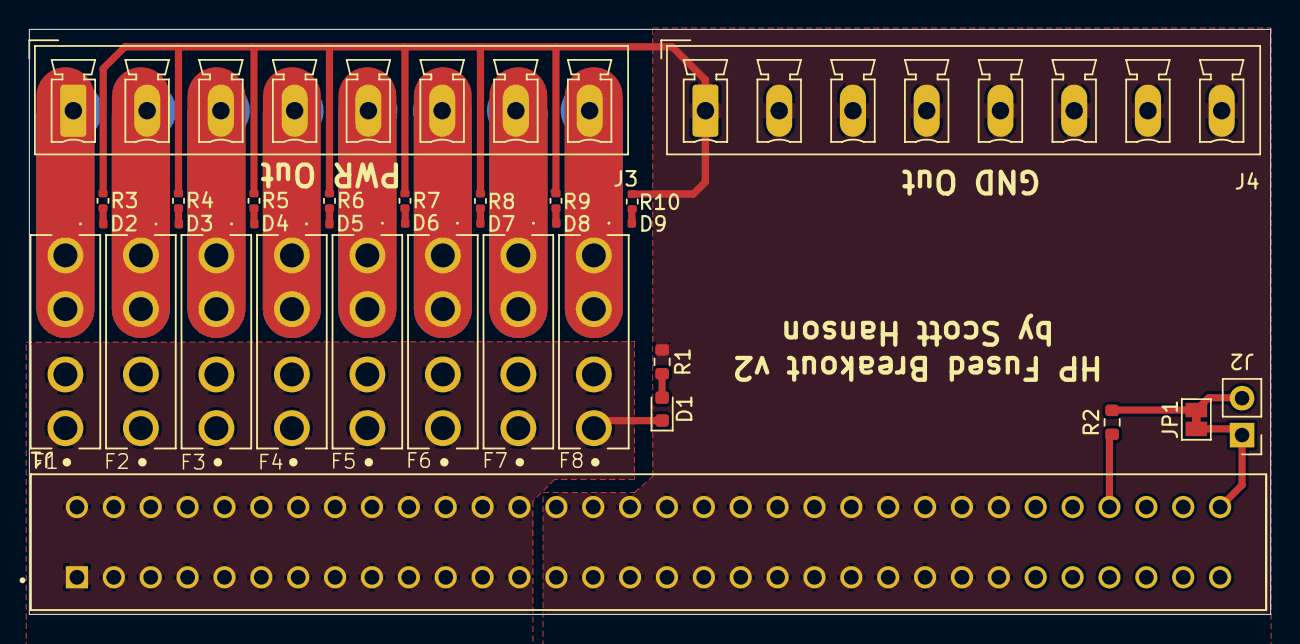
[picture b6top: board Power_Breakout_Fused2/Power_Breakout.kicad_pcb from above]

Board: 2 copper layers, 85.5 x 40.3 mm, 32 parts (0 on the bottom side), 22 nets.

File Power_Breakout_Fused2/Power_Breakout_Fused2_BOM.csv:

"Reference","Value","Footprint","Qty","DNP","Digi-Key PN","LCSC","MPN"
"D1","Power LED","LED_SMD:LED_0603_1608Metric","1","","160-1436-1-ND","C2286","LTST-C190KRKT"
"D2,D3,D4,D5,D6,D7,D8,D9","LED","LED_SMD:LED_0402_1005Metric","8","","1516-1216-1-ND","C434449","QBLP595-IG"
"F1,F2,F3,F4,F5,F6,F7,F8","3544-2_SM","3544-2:FUSE_3544-2","8","","36-3544-2-ND","C492610","3544-2"
"J1","PS Conn","TE_1761469-1:TE_1761469-1","1","","A102052-ND","","1761468-1"
"J2","Conn_01x02_Male","Connector_PinHeader_2.54mm:PinHeader_1x02_P2.54mm_Vertical","1","DNP","","",""
"J3","PWR Out","Connector_Phoenix_MC_HighVoltage:PhoenixContact_MCV_1,5_8-G-5.08_1x08_P5.08mm_Vertical","1","","609-3942-ND","","VI0821550000G"
"J4","GND Out","Connector_Phoenix_MC_HighVoltage:PhoenixContact_MCV_1,5_8-G-5.08_1x08_P5.08mm_Vertical","1","","609-3942-ND","","VI0821550000G"
"JP1","SolderJumper_2_Bridged","Jumper:SolderJumper-2_P1.3mm_Bridged_Pad1.0x1.5mm","1","","","",""
"R1","2.2K","Resistor_SMD:R_0603_1608Metric","1","","311-2.20KHRCT-ND","C4190","RC0603FR-072K2L"
"R2","100","Resistor_SMD:R_0603_1608Metric","1","","311-100HRCT-ND","C22775","RC0603FR-07100RL"
"R3,R4,R5,R6,R7,R8,R9,R10","2.2K","Resistor_SMD:R_0402_1005Metric","8","","311-2.20KLRCT-ND","C25879","RC0402FR-072K2L"

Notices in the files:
parts and their libraries:
Copyright 2021 Accelerated Designs. All rights reserved.
